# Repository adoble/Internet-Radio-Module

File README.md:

# Modular Audio Project - Internet Radio Module

An internet radio source that (eventually) should  communicate with the other modules (such as the amplifier) using I2S (or something similar).

The current version does not output I2S, but instead a normal stereo audio signal.

## System Diagram

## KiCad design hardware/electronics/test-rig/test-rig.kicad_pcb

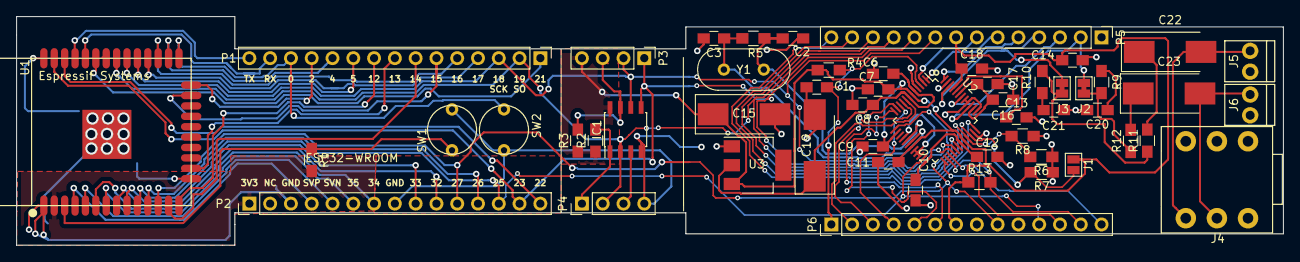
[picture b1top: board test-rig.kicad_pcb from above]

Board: 2 copper layers, 154.8 x 27.9 mm, 53 parts (0 on the bottom side), 60 nets.

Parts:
C1, C6, C7, C8, C9, C10, C11, C12, C16, C17, C18: 100n; C_0805_HandSoldering
C2, C3: 22p; C_0805_HandSoldering
C13: 1u; C_0805_HandSoldering
C14: 10u; C_0805_HandSoldering
C15, C19: 10u; CP_Tantalum_Case-D_EIA-7343-31_Hand
C20, C21: 10n; C_0805_HandSoldering
C22, C23: 220u; CP_Tantalum_Case-D_EIA-7343-31_Hand
IC1: 23LC1024; SOIC-8_3.9x4.9mm_Pitch1.27mm
J1: JUMPER_OPEN; SolderJumper-2_P1.3mm_Open_Pad1.0x1.5mm
J2, J3: JUMPER_CLOSED; SolderJumper-2_P1.3mm_Bridged_Pad1.0x1.5mm
J4: AudioJack3_Switch; Stereo_Jack-Socket_6_Pin
J5, J6: Screw_Terminal_1x02
P1, P2: CONN_01X15; Pin_Header_Straight_1x15_Pitch2.54mm
P3, P4: CONN_01X04; Pin_Header_Straight_1x04_Pitch2.54mm
P5, P6: CONN_01X14; Pin_Header_Straight_1x14_Pitch2.54mm
R1, R2, R3: 10K; R_0805_HandSoldering
R4, R6, R7, R8: 100K; R_0805_HandSoldering
R5: 1M; R_0805_HandSoldering
R9, R10: 22; R_0805_HandSoldering
R11, R12: 100; R_0805_HandSoldering
R13: 100k; R_0805_HandSoldering
SW1: RST; SW-PUSH-RND-SMALL
SW2: 0; SW-PUSH-RND-SMALL
U1: ESP32-WROOM-32; ESP32-WROOM-32-Espressif-Symbol-Kicad-62379
U2: VS1053B; LQFP-48_7x7mm_Pitch0.5mm
U3: LM1117-1.8; SOT-223
Y1: 12.288MHz; Crystal_HC49-U_Vertical

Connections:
+1.8V: C6.1, C8.1, C10.1, C12.1, C19.1, U2.5, U2.7, U2.24, U2.31, U3.2
+3V3: C7.1, C9.1, C11.1, C14.1, C15.1, C16.1, C17.1, C18.1, IC1.8, J1.1, P2.1, P3.4, P5.8, P6.7, R1.1, R2.1, R3.1, R4.2, R13.1, U1.2, U2.6, U2.14, U2.19, U2.32, U2.38, U2.43, U2.45, U3.3
/DREQ/IO26: P2.12, P6.2, U1.11, U2.8
/EN: R1.2, SW1.1, U1.3
/GBUF: P5.3, U2.42
/GPIO0: P5.12, R6.2, R8.2, U2.33
/GPIO1: J1.2, P5.13, R7.2, U2.34
/GPIO2: P6.3, U2.9
/GPIO3: P6.4, U2.10
/IO0: P1.13, SW2.1, U1.25
/IO2: P1.12, U1.24
/IO4: P1.11, U1.26
/IO5: P1.10, U1.29
/IO12: P1.9, U1.14
/IO13: P1.8, U1.16
/IO14: P1.7, U1.13
/IO15: P1.6, U1.23
/IO16: P1.5, U1.27
/IO17: P1.4, U1.28
/IO21: P1.1, U1.33
/IO32: P2.10, U1.8
/IO33: P2.9, U1.9
/IO34: P2.7, U1.6
/IO35: P2.6, U1.7
/LEFT: J3.1, P5.4, U2.46
/LINE2: P5.5, U2.48
/LROUT/GPIO4: P5.14, U2.36
/L_OUT: C22.2, J4.T, J5.2
/MCLK/GPIO5: P6.12, U2.25
/MICN: P5.7, U2.2
/MICP/LINE1: P5.6, U2.1
/MP3RST: C1.1, P6.1, R4.1, U2.3
/RAM-CS/IO22: IC1.1, P2.15, P4.1, R2.2, U1.36
/RIGHT: J2.1, P5.2, U2.39
/RX: P6.13, R13.2, U2.26
/RXDO: P1.14, U1.34
/R_OUT: C23.2, J4.R, J6.2
/SCK/IO18: IC1.6, P1.3, P3.2, P5.9, U1.30, U2.28
/SCLK/GPIO6: P6.5, U2.11
/SDATA/GPIO7: P6.6, U2.12
/SENSOR_VN: P2.5, U1.5
/SENSOR_VP: P2.4, U1.4
/SI/IO23: IC1.5, P2.14, P3.1, P5.10, U1.37, U2.29
/SIO2: IC1.3, P4.3
/SO/IO19: IC1.2, P1.2, P4.2, P5.11, U1.31, U2.30
/TX: P6.14, U2.27
/TXD0: P1.15, U1.35
/XCS/IO25: P2.13, P6.11, U1.10, U2.23
/XDCS/IO27: P2.11, P6.9, U1.12, U2.13
/~HOLD/~SIO3: IC1.7, P3.3, R3.2
AGND: C1.2, C2.2, C3.2, C6.2, C7.2, C8.2, C9.2, C10.2, C11.2, C12.2, C13.2, C14.2, C15.2, C16.2, C17.2, C18.2, C19.2, C20.2, C21.2, IC1.4, J4.S, J5.1, J6.1, P2.3, P2.8, P4.4, P5.1, P6.8, R6.1, R7.1, R8.1, SW1.2, SW2.2, U1.1, U1.15, U1.38, U1.39, U2.4, U2.16, U2.20, U2.21, U2.22, U2.35, U2.37, U2.40, U2.41, U2.47, U3.1
unnamed: C2.1, R5.2, U2.17, Y1.1
unnamed: C3.1, R5.1, U2.18, Y1.2
unnamed: C13.1, U2.44
unnamed: C20.1, R9.2
unnamed: C21.1, R10.2
unnamed: C22.1, R11.2
unnamed: C23.1, R12.2
unnamed: J2.2, R9.1, R12.1
unnamed: J3.2, R10.1, R11.1

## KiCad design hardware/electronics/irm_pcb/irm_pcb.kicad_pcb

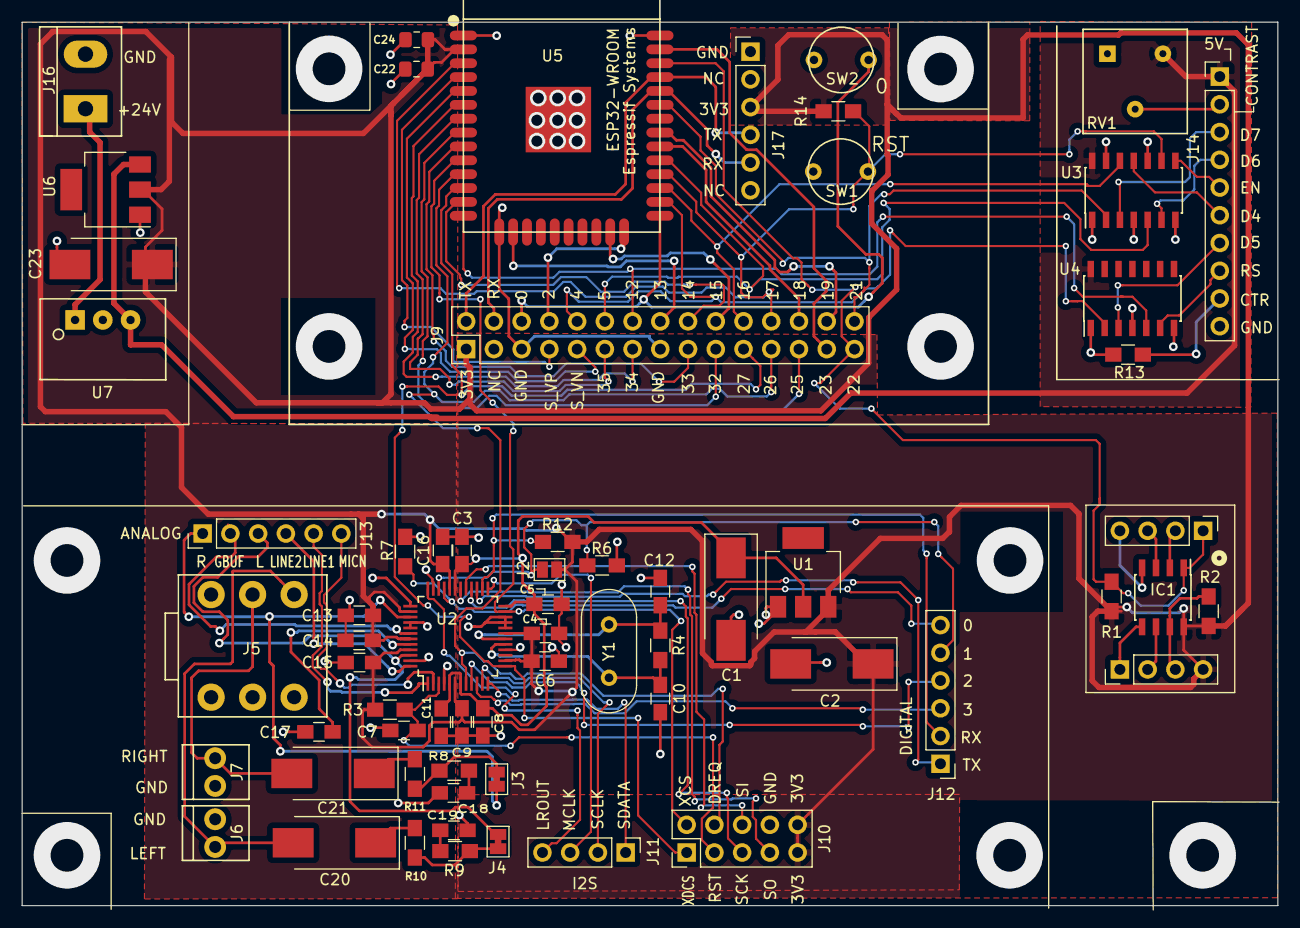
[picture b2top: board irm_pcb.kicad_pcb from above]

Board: 2 copper layers, 115.0 x 80.9 mm, 65 parts (0 on the bottom side), 75 nets.

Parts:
C1, C2, C23: 10u; CP_Tantalum_Case-D_EIA-7343-31_Hand
C3, C4, C5, C6, C7, C8, C9, C11, C14, C15, C16: 100n; C_0805_HandSoldering
C10, C12: 22p; C_0805_HandSoldering
C13: 10u; C_0805_HandSoldering
C17: 1u; C_0805_HandSoldering
C18, C19: 10n; C_0805_HandSoldering
C20, C21: 220u; CP_Tantalum_Case-D_EIA-7343-31_Hand
C22: 10u; C_0805_2012Metric_Pad1.15x1.40mm_HandSolder
C24: 100n; C_0805_2012Metric_Pad1.15x1.40mm_HandSolder
IC1: 23LC1024; SOIC-8_3.9x4.9mm_Pitch1.27mm
J1, J8, J11: Conn_01x04; Pin_Header_Straight_1x04_Pitch2.54mm
J2: JUMPER_OPEN; SolderJumper-2_P1.3mm_Open_Pad1.0x1.5mm
J3, J4: JUMPER_CLOSED; SolderJumper-2_P1.3mm_Bridged_Pad1.0x1.5mm
J5: AudioJack3_Switch; Stereo_Jack-Socket_6_Pin
J6, J7: Screw_Terminal_1x02
J9: Conn_02x15_Top_Bottom; Pin_Header_Straight_2x15_Pitch2.54mm
J10: Conn_02x05_Counter_Clockwise; Pin_Header_Straight_2x05_Pitch2.54mm_CC
J12, J13, J17: Conn_01x06; Pin_Header_Straight_1x06_Pitch2.54mm
J14: Conn_01x10; Pin_Header_Straight_1x10_Pitch2.54mm
J16: Screw_Terminal_01x02; Screw_Terminal_1x02_Pitch5.00mm
R1, R2, R13, R14: 10K; R_0805_HandSoldering
R3, R6, R7: 100K; R_0805_HandSoldering
R4: 1M; R_0805_HandSoldering
R8, R9: 22; R_0805_HandSoldering
R10, R11: 100; R_0805_HandSoldering
R12: 100k; R_0805_HandSoldering
RV1: 10K; Potentiometer_Trimmer_Bourns_3386F
SW1: RST; SW-PUSH-RND-SMALL
SW2: 0; SW-PUSH-RND-SMALL
U1: LM1117-1.8; SOT-223
U2: VS1053B; LQFP-48_7x7mm_Pitch0.5mm
U3, U4: 74LS125; SOIC-14_3.9x8.7mm_Pitch1.27mm
U5: ESP32-WROOM-32; ESP32-WROOM-32-Espressif-Symbol-Kicad-62379
U6: LM1117-3.3; SOT-223
U7: TSR1-2450; TSR1-24_TO-220-3_V
Y1: 12.288MHz; Crystal_HC49-U_Vertical

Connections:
+1.8V: C1.1, C3.1, C5.1, C8.1, C11.1, U1.2, U2.5, U2.7, U2.24, U2.31
+3V3: C2.1, C4.1, C6.1, C9.1, C13.1, C14.1, C15.1, C16.1, C22.1, C23.1, C24.1, IC1.8, J2.1, J8.4, J9.1, J10.5, J10.6, J17.3, R1.1, R2.1, R3.2, R12.1, R14.1, U1.3, U2.6, U2.14, U2.19, U2.32, U2.38, U2.43, U2.45, U5.2, U6.2
+5V: J14.1, RV1.3, U3.14, U4.14, U6.3, U7.3
+24V: J16.1, U7.1
/Buffer RAM/RAM-CS: IC1.1, J1.1, J9.15, R1.2, U5.36
/Buffer RAM/SCK: IC1.6, J8.2
/Buffer RAM/SI: IC1.5, J8.1
/Buffer RAM/SIO2: IC1.3, J1.3
/Buffer RAM/SO: IC1.2, J1.2
/Buffer RAM/~HOLD/~SIO3: IC1.7, J8.3, R2.2
/Control/CONTRAST: J14.2, RV1.2
/Control/CONTROL: J14.9, R13.1
/Control/D4: J9.26, U3.12, U5.27
/Control/D4_EXT: J14.6, U3.11
/Control/D5: J9.20, U4.2, U5.26
/Control/D5_EXT: J14.7, U4.3
/Control/D6: J9.21, U3.5, U5.29
/Control/D6_EXT: J14.4, U3.6
/Control/D7: J9.30, U3.2, U5.33
/Control/D7_EXT: J14.3, U3.3
/Control/EN: J9.27, R14.2, SW1.1, U3.9, U5.3, U5.28
/Control/EN_EXT: J14.5, U3.8
/Control/RS: J9.22, U4.5, U5.14
/Control/RS_EXT: J14.8, U4.6
/MP3 Codec/DREQ: J9.12, J10.9, U2.8, U5.11
/MP3 Codec/GBUF: J13.2, U2.42
/MP3 Codec/GPIO0: J12.6, R7.2, U2.33
/MP3 Codec/GPIO1: J2.2, J12.5, R6.2, U2.34
/MP3 Codec/GPIO2: J12.4, U2.9
/MP3 Codec/GPIO3: J12.3, U2.10
/MP3 Codec/LEFT: J4.1, J13.3, U2.46
/MP3 Codec/LINE2: J13.4, U2.48
/MP3 Codec/LROUT/GPIO4: J11.4, U2.36
/MP3 Codec/L_OUT: C20.2, J5.T, J6.2
/MP3 Codec/MCLK/GPIO5: J11.3, U2.25
/MP3 Codec/MICN: J13.6, U2.2
/MP3 Codec/MICP/LINE1: J13.5, U2.1
/MP3 Codec/MP3RST: C7.1, J10.2, R3.1, U2.3
/MP3 Codec/RIGHT: J3.1, J13.1, U2.39
/MP3 Codec/RX: J12.2, R12.2, U2.26
/MP3 Codec/R_OUT: C21.2, J5.R, J7.1
/MP3 Codec/SCK: J10.3, U2.28
/MP3 Codec/SCLK/GPIO6: J11.2, U2.11
/MP3 Codec/SDATA/GPIO7: J11.1, U2.12
/MP3 Codec/SI: J10.8, U2.29
/MP3 Codec/SO: J10.4, U2.30
/MP3 Codec/TX: J12.1, U2.27
/MP3 Codec/XCS: J9.13, J10.10, U2.23, U5.10
/MP3 Codec/XDCS: J9.11, J10.1, U2.13, U5.12
/WROOM Processor/IO0: J9.18, SW2.1, U5.25
/WROOM Processor/IO2: J9.19, U5.24
/WROOM Processor/IO13: J9.23, U5.16
/WROOM Processor/IO14: J9.24, U5.13
/WROOM Processor/IO15: J9.25, U5.23
/WROOM Processor/IO32: J9.10, U5.8
/WROOM Processor/IO33: J9.9, U5.9
/WROOM Processor/IO34: J9.7, U5.6
/WROOM Processor/IO35: J9.6, U5.7
/WROOM Processor/RXDO: J9.17, J17.5, U5.34
/WROOM Processor/SCK: J9.28, U5.30
/WROOM Processor/SENSOR_VN: J9.5, U5.5
/WROOM Processor/SENSOR_VP: J9.4, U5.4
/WROOM Processor/SI: J9.14, U5.37
/WROOM Processor/SO: J9.29, U5.31
/WROOM Processor/TXD0: J9.16, J17.4, U5.35
AGND: C1.2, C2.2, C3.2, C4.2, C5.2, C6.2, C7.2, C8.2, C9.2, C10.2, C11.2, C12.2, C13.2, C14.2, C15.2, C16.2, C17.2, C18.2, C19.2, C22.2, C23.2, C24.2, IC1.4, J1.4, J5.S, J6.1, J7.2, J9.3, J9.8, J10.7, J14.10, J16.2, J17.1, R6.1, R7.1, R13.2, RV1.1, SW1.2, SW2.2, U1.1, U2.4, U2.16, U2.20, U2.21, U2.22, U2.35, U2.37, U2.40, U2.41, U2.47, U3.1, U3.4, U3.7, U3.10, U3.13, U4.1, U4.4, U4.7, U5.1, U5.15, U5.38, U5.39, U6.1, U7.2
unnamed: C10.1, R4.2, U2.17, Y1.1
unnamed: C12.1, R4.1, U2.18, Y1.2
unnamed: C17.1, U2.44
unnamed: C18.1, R8.2
unnamed: C19.1, R9.2
unnamed: C20.1, R10.2
unnamed: C21.1, R11.2
unnamed: J3.2, R8.1, R11.1
unnamed: J4.2, R9.1, R10.1

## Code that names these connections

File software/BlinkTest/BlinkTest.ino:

/*
 * Ocillates the signals on a set of pins.
 */

 const int DELAY = 100;


// LED Pins
//const int rs = 12, en = 2, d4 = 4, d5 = 17, d6 = 15, d7 = 5;  //DIFFERS FROM PCB DESIGN!

//VS1053 Pins
const int xcs = 25, dreq = 26, xdcs = 27, si = 23, so = 19, sck = 18, xrst = 33;
int pins[] = {xcs, dreq, xdcs, si, so, sck, xrst, -1}; // Terminated with a negative number


void setup() {
  

  for (int i = 0; pins[i] > 0 ; i++) {
    pinMode(pins[i], OUTPUT);
  }

  Serial.begin(115200);

 
}

void loop() {
  Serial.println("BlinkTest");
  
  for (int i = 0; pins[i] > 0; i++) {
    digitalWrite(pins[i], HIGH);   
  }
  
  delay(DELAY);    
                     
  for (int i = 0; pins[i] > 0; i++) {
    digitalWrite(pins[i], LOW);   
  }
 
  delay(DELAY);                      

}

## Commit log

2019-02-13 First working version with external DAC
2019-02-26 Pause/Mute button added (can mute radio), Button library added, cleaned up
2019-02-28 Station change from a simple push button
2019-02-28 Updated comments
2019-07-05 Lot of test files that will be later removed
2019-07-09 Corrected error with line terminators
2019-07-09 Station change logic working
2019-07-16 Still in construction
2019-07-18 Extended structure
2019-07-19 Main wiring diagram
2019-07-19 Contrast pot on PCB; Control button symbol changed
2019-07-21 Breadboard components added
2019-07-21 Added SparkFun library for ESP32 Thing board
2019-07-27 Added level shifting buffers
2019-07-27 Changed the pins for new circuit with VS1053
2019-08-02 Long station names now scroll
2019-08-02 Long station names now scroll. Code tidied up
2019-08-09 Radio working
2019-08-09 Added LCD with simple message
2019-08-10 Added simple LCD messages
2019-08-11 Using ESP8266Spiram library to correctly drive the 24LC1024
2019-08-13 Uses the Station class
2019-08-16 Correct reset
2019-08-16 Restructering so stations can be changed
2019-08-16 Tidied up code and comments
2019-08-16 Commented libraries
2019-08-16 Removed redundant references
2019-08-17 Added more stations
2019-08-25 Display more consistent
2019-08-25 Correct display behaviour
2019-08-31 Replaced stations
2019-08-31 Changes to display logic
2019-09-06 Added local libraries
2019-09-06 Corrected errors in station changing
2019-09-06 No longer using the ESP8266Audio lib
2019-10-06 Added test-rig project
2019-10-12 Test rig
2019-10-13 Added programming header
2019-10-22 failed-layout
2019-10-23 WROOM and MEM layout completed
2019-10-23 Removed double 10u decoupling caps in VS1053 power supply
2019-11-17 New schematic
2019-12-06 New borad layout - routing incomplete
2019-12-12 Routing completed
2019-12-13 Layout completed
2019-12-13 Board size reduced
2019-12-14 Rev 1
2019-12-14 Rev 1.1
2019-12-20 Added WROOM decoupling capacitors
2019-12-27 Added 3V3 copper flows
2020-01-02 Basic station changes work
2020-01-04 Connecting message has correct behaviour
2020-01-04 Removed commented out code
2020-03-29 Control sw working and wiring updated
2020-03-30 Radio, display and control button work
2020-04-12 Custom routines for HTTP connections to handle non-conforming IR stations
2020-04-12 Tidied up the code and comments
2020-04-14 Extended comments
2020-04-14 Refactor connectStation -> httpConnect plus simpler return code handling
2020-04-14 Added httpConnect helper function
2020-04-17 Now use custom HTTP connection code for all connections
2020-04-17 Removed WiFiMulti
2020-04-18 Stores last station played to EEPROM
2020-04-22 Test sketch to oscillator a set of pins
2020-04-22 Updated pins
2020-04-22 Updated the external wiring
2020-04-25 First draft front and rear panel design
2020-04-25 Removed redundant (test) sketches
2020-04-25 Moved test sketches into the test directory
2020-04-25 Deleted more redundant test routines
2020-04-25 Moved to test directory
2020-04-25 Documentation of test rountines
2020-04-25 Updated links
2020-04-25 README.md now says something meaningful.
2020-04-25 Changed to markdown format
2020-04-28 Removed homepage directory
2020-04-28 Production version
2020-04-28 Removed home(page) directory
2020-05-01 Increased volume for current amplifier
2020-05-01 Added system diagram
2020-05-01 Updated README with link to system diagram
